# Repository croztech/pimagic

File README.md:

PiMagic Interface Board Repository
==================================

Created by @croz_tech (http://croztech.wordpress.com/)

PiMagic repository contents:

hardware......... EAGLE hardware design files (schematic & PCB)

ana_pong.py...... Version of the popular Pong game using analogue paddle inputs

firmata_rgb.py... Random RGB LED mood lamp using PWM outputs of the PiMagic

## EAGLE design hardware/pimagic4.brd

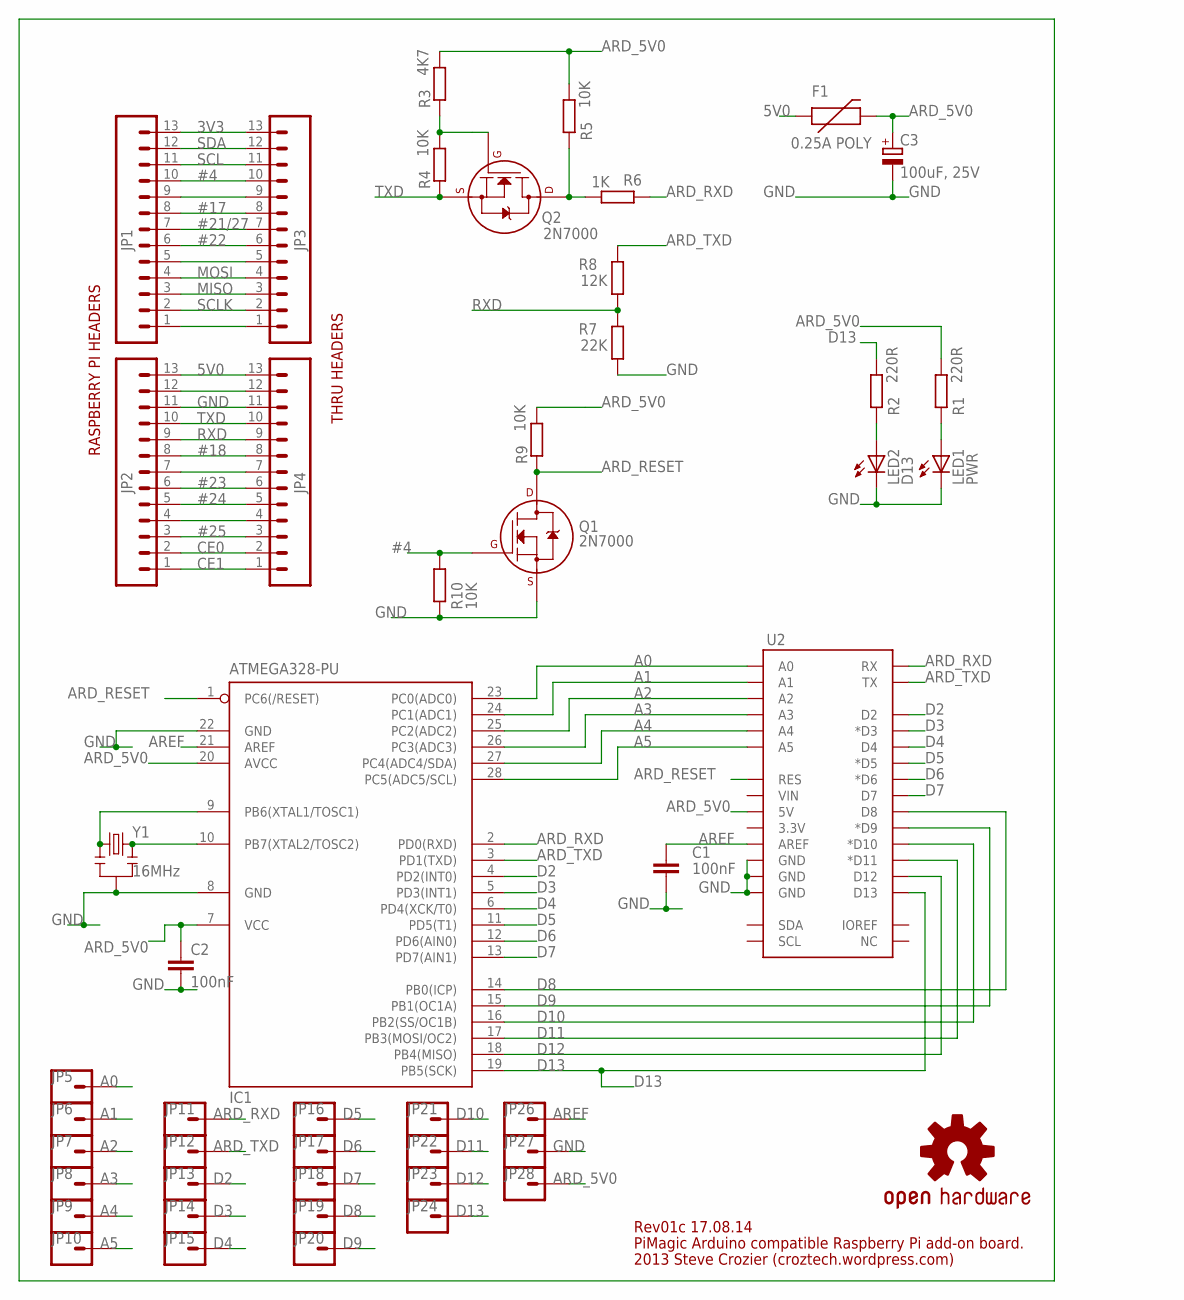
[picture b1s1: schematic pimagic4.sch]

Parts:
C1, C2: 100nF; C5B2.5
C3: 100uF, 25V; E2,5-6
F1: 0.25A POLY; PTC
IC1: ATMEGA328-PU; DIL28-3
JP1, JP2, JP3, JP4: M13; 1X13
JP5, JP6, JP7, JP8, JP9, JP10, JP11, JP12, JP13, JP14, JP15, JP16, JP17, JP18, JP19, JP20, JP21, JP22, JP23, JP24, JP26, JP27, JP28: M01PTH; 1X01
LED1: PWR; LED3MM
LED2: D13; LED3MM
Q1, Q2: 2N7000; TO-92
R1, R2: 220R; 0207/10
R3: 4K7; 0207/10
R4, R5, R9, R10: 10K; 0207/10
R6: 1K; 0207/10
R7: 22K; 0207/10
R8: 12K; 0207/10
U2: ARDUINO_SHIELDLONGPADS; DUEMILANOVE_SHIELD_LONGPADS
U$1: OSHW-LOGOM; OSHW-LOGO-M
Y1: 16MHz; RESONATOR-PTH

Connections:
3V3: JP1.13, JP3.13
5V0: F1.P$1 (1), JP2.13, JP4.13
#4: JP1.10, JP3.10, Q1.2 (G), R10.2
#17: JP1.8, JP3.8
#18: JP2.8, JP4.8
#21/27: JP1.7, JP3.7
#22: JP1.6, JP3.6
#23: JP2.6, JP4.6
#24: JP2.5, JP4.5
#25: JP2.3, JP4.3
A0: IC1.23 (PC0(ADC0)), JP5.1, U2.A0
A1: IC1.24 (PC1(ADC1)), JP6.1, U2.A1
A2: IC1.25 (PC2(ADC2)), JP7.1, U2.A2
A3: IC1.26 (PC3(ADC3)), JP8.1, U2.A3
A4: IC1.27 (PC4(ADC4/SDA)), JP9.1, U2.A4
A5: IC1.28 (PC5(ADC5/SCL)), JP10.1, U2.A5
ARD_5V0: C2.1, C3.+, F1.P$2 (2), IC1.7 (VCC), IC1.20 (AVCC), JP28.1, R1.2, R3.2, R5.2, R9.2, U2.5V
ARD_RESET: IC1.1 (PC6(/RESET)), Q1.3 (D), R9.1, U2.RES
ARD_RXD: IC1.2 (PD0(RXD)), JP11.1, R6.1, U2.RX
ARD_TXD: IC1.3 (PD1(TXD)), JP12.1, R8.1, U2.TX
AREF: C1.1, IC1.21 (AREF), JP26.1, U2.AREF
CE0: JP2.2, JP4.2
CE1: JP2.1, JP4.1
D2: IC1.4 (PD2(INT0)), JP13.1, U2.D2
D3: IC1.5 (PD3(INT1)), JP14.1, U2.D3 (*D3)
D4: IC1.6 (PD4(XCK/T0)), JP15.1, U2.D4
D5: IC1.11 (PD5(T1)), JP16.1, U2.D5 (*D5)
D6: IC1.12 (PD6(AIN0)), JP17.1, U2.D6 (*D6)
D7: IC1.13 (PD7(AIN1)), JP18.1, U2.D7
D8: IC1.14 (PB0(ICP)), JP19.1, U2.D8
D9: IC1.15 (PB1(OC1A)), JP20.1, U2.D9 (*D9)
D10: IC1.16 (PB2(SS/OC1B)), JP21.1, U2.D10 (*D10)
D11: IC1.17 (PB3(MOSI/OC2)), JP22.1, U2.D11 (*D11)
D12: IC1.18 (PB4(MISO)), JP23.1, U2.D12
D13: IC1.19 (PB5(SCK)), JP24.1, R2.2, U2.D13
GND: C1.2, C2.2, C3.-, IC1.8 (GND), IC1.22 (GND), JP2.11, JP4.11, JP27.1, LED1.K (C), LED2.K (C), Q1.1 (S), R7.2, R10.1, U2.GND@0 (GND), U2.GND@1 (GND), U2.GND@2 (GND), Y1.2
MISO: JP1.3, JP3.3
MOSI: JP1.4, JP3.4
unnamed: JP1.5, JP3.5
unnamed: JP1.1, JP3.1
unnamed: Q2.2 (G), R3.1, R4.2
unnamed: IC1.9 (PB6(XTAL1/TOSC1)), Y1.1
unnamed: JP1.9, JP3.9
unnamed: IC1.10 (PB7(XTAL2/TOSC2)), Y1.3
unnamed: Q2.3 (D), R5.1, R6.2
unnamed: LED2.A, R2.1
unnamed: LED1.A, R1.1
unnamed: JP2.12, JP4.12
unnamed: JP2.7, JP4.7
unnamed: JP2.4, JP4.4
RXD: JP2.9, JP4.9, R7.1, R8.2
SCL: JP1.11, JP3.11
SCLK: JP1.2, JP3.2
SDA: JP1.12, JP3.12
TXD: JP2.10, JP4.10, Q2.1 (S), R4.1

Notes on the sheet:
RASPBERRY PI HEADERS
THRU HEADERS
PiMagic Arduino compatible Raspberry Pi add-on board.
2013 Steve Crozier (croztech.wordpress.com)
Rev01c 17.08.14

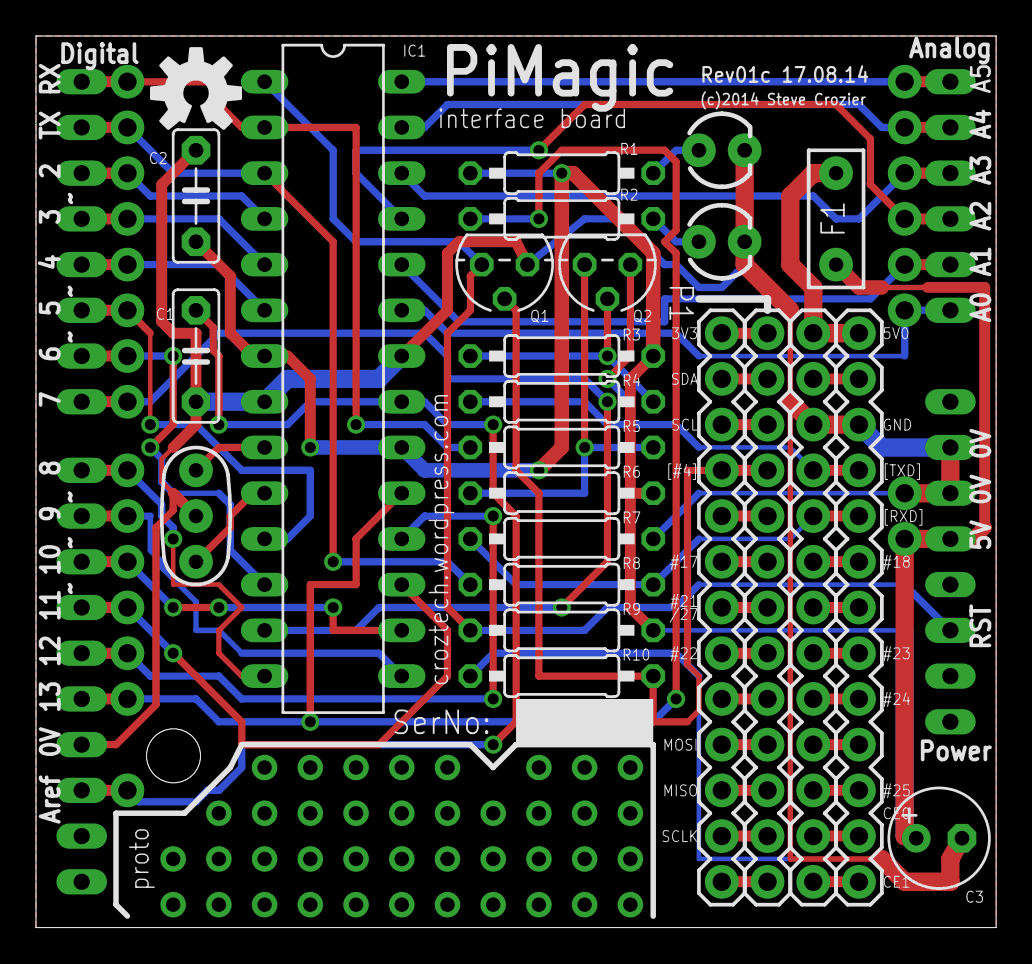
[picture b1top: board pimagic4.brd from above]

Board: 2 copper layers, 53.3 x 49.5 mm, 49 parts (1 on the bottom side), 55 nets.

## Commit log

2014-08-07 Create firmata_rgb.py
    Python Firmata test for PiMagic board. Use with an RGB LED connected on PWM pins D3,5,6
2014-08-10 Create ana_pong.py
    Analogue PiPong using the PiMagic interface board, channels A0/A1
    - Note that the first version has only one analogue paddle on A0
2014-08-10 Update ana_pong.py
    Fixed the window title
2014-08-10 Update ana_pong.py
    - Added second channel code
    - Removed unused methods now the keyboard isn't used
2014-08-10 PiMagic hardware design
    Hardware design files (schematic & board layout) for Eagle CAD 6.4.x
2014-08-12 Update README.md
    Updated descriptions
2014-08-12 Update README.md
    Fixed formatting
2014-09-16 Rev01c update
    - Q1/Q2 silkscreen corrected
    - some of the silkscreen logos are now corrected
    - there’s a nice ground plan copper pour added on both sides
    - files updated to Eagle 7.1.0 format
2014-09-16 Gerber files for PCB production
    Rev01c
    Top and bottom copper (.GTL, .GBL)
    Top and bottom solder mask (.GTS, .GBS)
    Top silkscreen (.GTO)
    Drill file, 2.4 leading (.TXT)

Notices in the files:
hardware/pimagic4.brd:
(c)2014 Steve Crozier
parts and their libraries:
SparkFun: Licensing: CC v3.0 Share-Alike You are welcome to use this library for commercial purposes.
